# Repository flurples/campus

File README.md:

# campus
mechanical keyboard conversion for a framework 13

build video: https://youtu.be/kGHAUogFsYY

## about
campus is designed to be a drop-in replacement housing for a framework 13 that features a hhkb layout kailh choc mechanical keyboard.

## you will need
- a framework 13 laptop
#### bottom chassis parts
- bottom chassis (cnc)
- bottom-bracket-R, L & M (3d print)
#### input cover parts
- input cover (cnc)
- plate (cnc)
- 3x knobs (cnc)
- 1x touchpad-clamp-R & L (3d print)
- 2x touchpad-clamp-top (3d print)
#### lid parts
- lid (cnc)
- bezel (3d print)
- lid-corner-cap-R & L (3d print)
#### other hardware
- 60x kailh choc switches
- choc stabilizers (2x 2u, 1x 6.25u)
- compatible keycaps (be sure to get 6.25u space, 1.75u shift, etc)
- 3x ec12 low profile encoders
- m1.6 x 3mm heat set inserts
- m2 x 4mm heat set inserts
- m2 x 2.5mm heat set inserts
- 5x m2 x 20mm flat head hex screws (to screw the chassis together)
- 3x m2 x 8mm set screws (for the knobs)
- 4x 1" OD rubber bumpers
- variety of double sided tapes
- epoxy

## build notes
bottom chassis, input cover, lid, knobs, and plate were cnc'd from aluminum. all 3d printed parts were printed in petg to avoid breaking down over the years. heat set inserts for screw holes to mount factory components are installed into the bottom-brackets, which are then epoxied to the bottom-chassis. due to jlcpcb's minimum thickness requirements, the input and lid do not use heat set inserts. instead, the aluminum is directly tapped.

#### the keyboard workaround
the usb hub was too complex and I wasn't able to get it working. because the keyboard was originally meant to connect internally through the usb hub, I ended up simply bypassing the usb hub entirely, bypassing it with a unified daughterboard s1.
in case anyone wants to attempt to diagnose why, I've uploaded the kicad files as is for reference.

## disclaimer
campus is a highly involved project and will require completely tearing down your framework laptop and transplanting all the components into an objectively worse-designed chassis than the factory framework chassis. some features will be lost, for example, the privacy switches built into the webcam module, or the little buttons that lock the expansion cards in place. I am not a professional electronics designer, so expect to perform some janky workarounds to get the laptop functioning as it should. I am not responsible for any issues you may encounter with the build, so please use the files with caution.

I do not sell any products, and I am not affiliated with any vendors who claim to sell my designs. if you choose to support these vendors, I am not responsible for any issues you may encounter with them.

## gallery

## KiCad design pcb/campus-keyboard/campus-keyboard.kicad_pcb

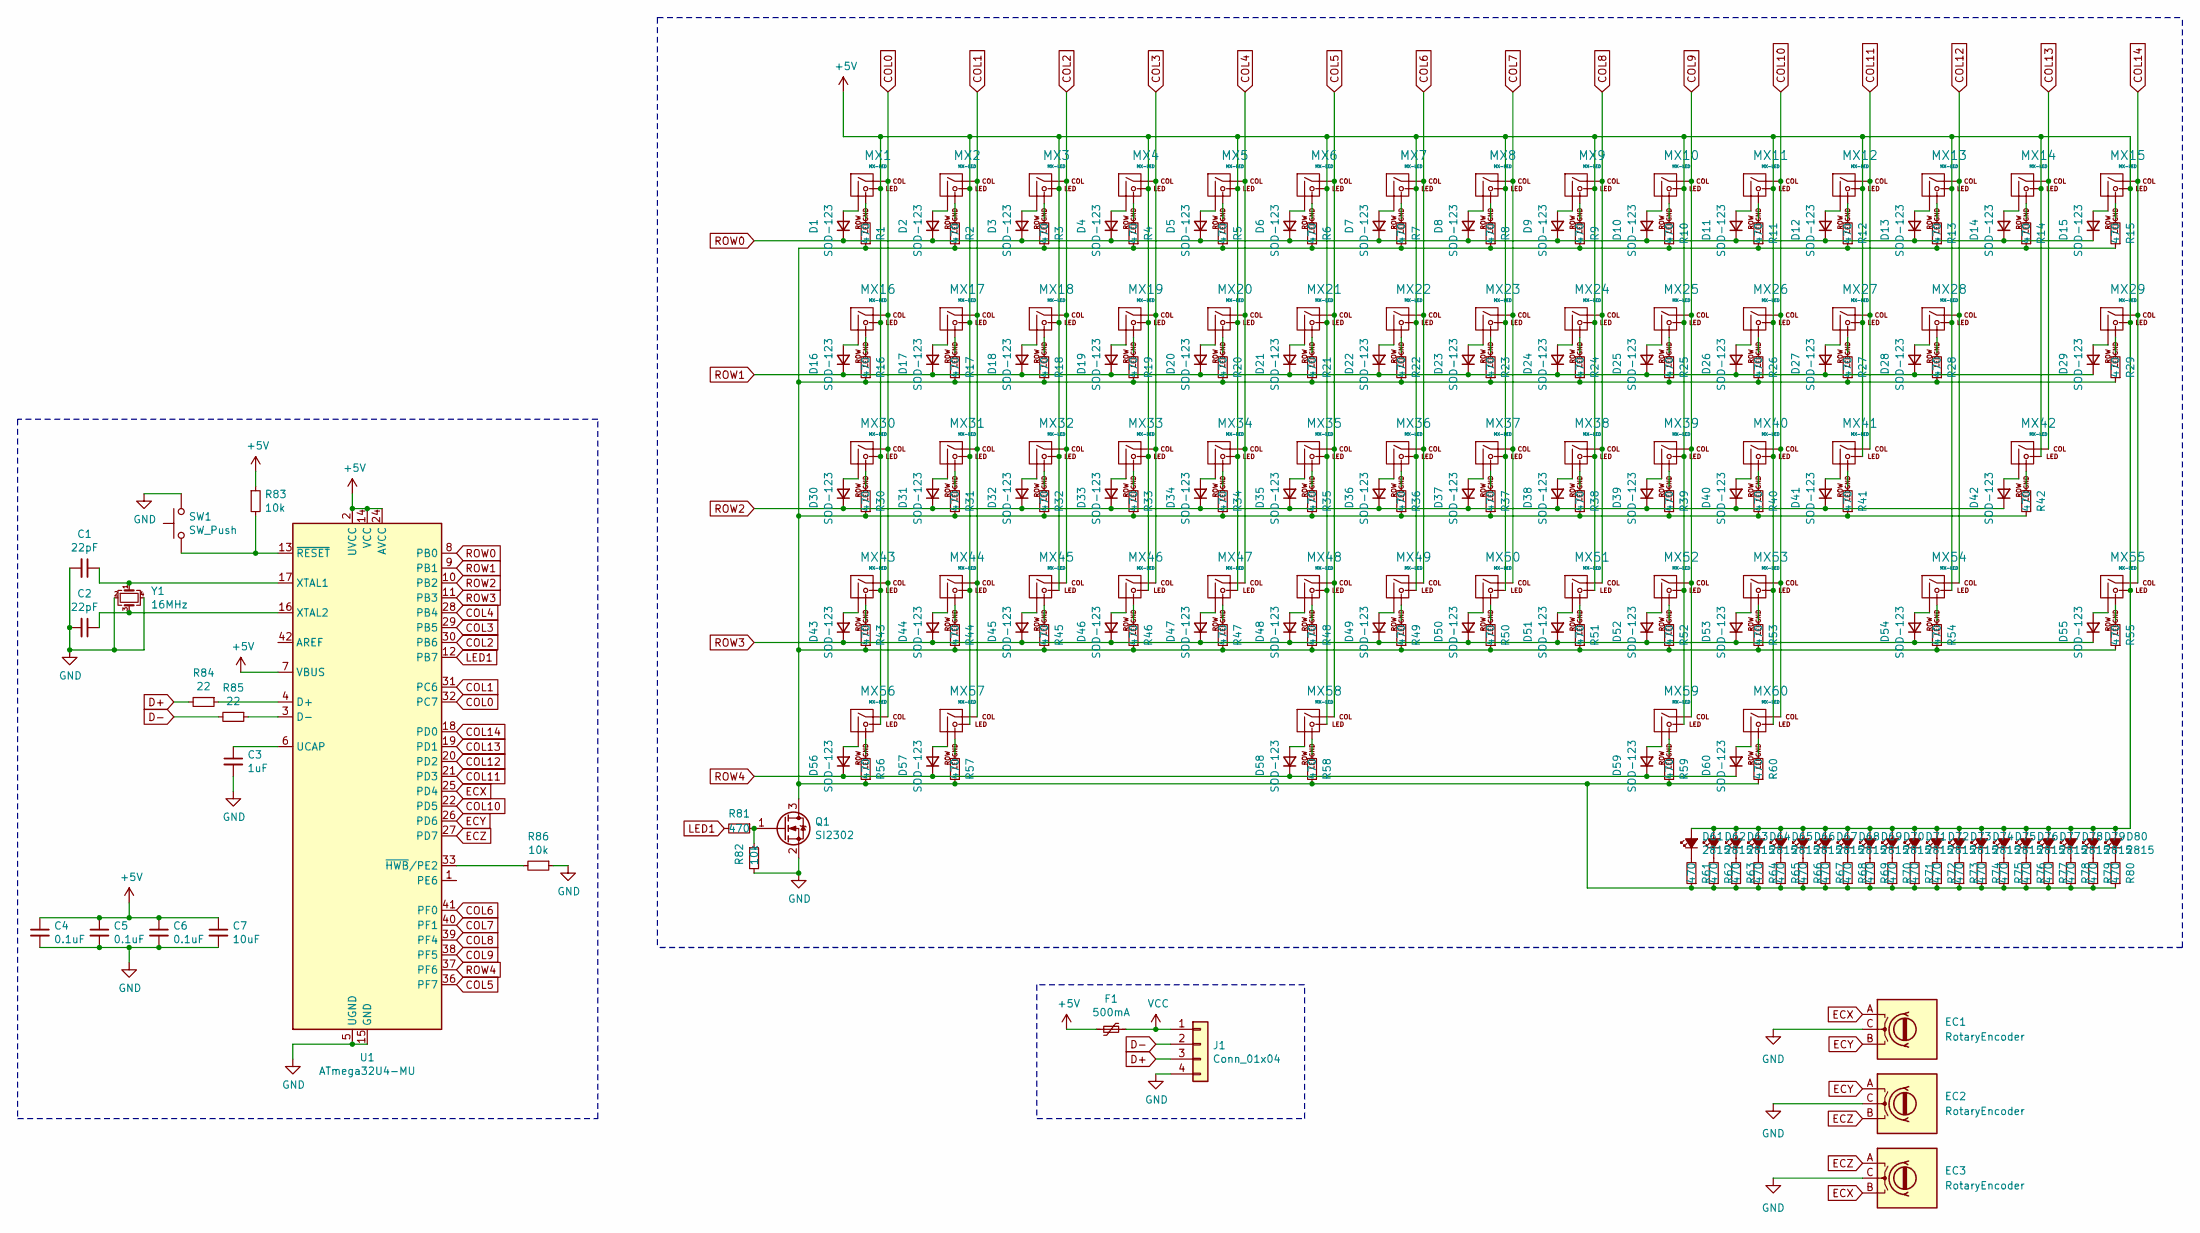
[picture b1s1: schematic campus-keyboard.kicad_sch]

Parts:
C1, C2: 22pF; C_0805_2012Metric
C3: 1uF; C_0805_2012Metric
C4, C5, C6: 0.1uF; C_0805_2012Metric
C7: 10uF; C_0805_2012Metric
D1, D2, D3, D4, D5, D6, D7, D8, D9, D10, D11, D12, D13, D14, D15, D16, D17, D18, D19, D20, D21, D22, D23, D24, D25, D26, D27, D28, D29, D30, D31, D32, D33, D34, D35, D36, D37, D38, D39, D40, D41, D42, D43, D44, D45, D46, D47, D48, D49, D50, D51, D52, D53, D54, D55, D56, D57, D58, D59, D60: SOD-123; D_SOD-123-CenterREF__
D61, D62, D63, D64, D65, D66, D67, D68, D69, D70, D71, D72, D73, D74, D75, D76, D77, D78, D79, D80: 2815; GW JCLPS2.EM
EC1, EC2, EC3: RotaryEncoder; SW3_EC12E1220301_ALPS
F1: 500mA; Fuse_1206_3216Metric
J1: Conn_01x04; Molex_Pico-EZmate_78171-0004_1x04-1MP_P1.20mm_Vertical
MX1, MX2, MX3, MX4, MX5, MX6, MX7, MX8, MX9, MX10, MX11, MX12, MX13, MX14, MX15, MX17, MX18, MX19, MX20, MX21, MX22, MX23, MX24, MX25, MX26, MX27, MX28, MX31, MX32, MX33, MX34, MX35, MX36, MX37, MX38, MX39, MX40, MX41, MX44, MX45, MX46, MX47, MX48, MX49, MX50, MX51, MX52, MX53, MX55: MX-LED; Choc-1u-GW
MX16, MX29: MX-LED; Choc-1.5u-GW
MX30, MX54: MX-LED; Choc-1.75u-GW
MX42, MX43: MX-LED; Choc-2.25u-GW
MX56, MX57, MX59, MX60: MX-LED; Choc-1.25u-GW
MX58: MX-LED; Choc-6.25u-GW
Q1: SI2302; SOT-23
R1, R2, R3, R4, R5, R6, R7, R8, R9, R10, R11, R12, R13, R14, R15, R16, R17, R18, R19, R20, R21, R22, R23, R24, R25, R26, R27, R28, R29, R30, R31, R32, R33, R34, R35, R36, R37, R38, R39, R40, R41, R42, R43, R44, R45, R46, R47, R48, R49, R50, R51, R52, R53, R54, R55, R56, R57, R58, R59, R60, R61, R62, R63, R64, R65, R66, R67, R68, R69, R70, R71, R72, R73, R74, R75, R76, R77, R78, R79, R80, R81: 470; R_0805_2012Metric-CenterREF__
R82, R83, R86: 10k; R_0805_2012Metric-CenterREF__
R84, R85: 22; R_0805_2012Metric-CenterREF__
SW1: SW_Push; SKQG-1155865
U1: ATmega32U4-MU; QFN-44-1EP_7x7mm_P0.5mm_EP5.2x5.2mm
Y1: 16MHz; Crystal_SMD_3225-4Pin_3.2x2.5mm

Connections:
+5V: C4.1, C5.1, C6.1, C7.1, D61.2 (A), D62.2 (A), D63.2 (A), D64.2 (A), D65.2 (A), D66.2 (A), D67.2 (A), D68.2 (A), D69.2 (A), D70.2 (A), D71.2 (A), D72.2 (A), D73.2 (A), D74.2 (A), D75.2 (A), D76.2 (A), D77.2 (A), D78.2 (A), D79.2 (A), D80.2 (A), F1.2, MX1.3 (LED), MX2.3 (LED), MX3.3 (LED), MX4.3 (LED), MX5.3 (LED), MX6.3 (LED), MX7.3 (LED), MX8.3 (LED), MX9.3 (LED), MX10.3 (LED), MX11.3 (LED), MX12.3 (LED), MX13.3 (LED), MX14.3 (LED), MX15.3 (LED), MX16.3 (LED), MX17.3 (LED), MX18.3 (LED), MX19.3 (LED), MX20.3 (LED), MX21.3 (LED), MX22.3 (LED), MX23.3 (LED), MX24.3 (LED), MX25.3 (LED), MX26.3 (LED), MX27.3 (LED), MX28.3 (LED), MX29.3 (LED), MX30.3 (LED), MX31.3 (LED), MX32.3 (LED), MX33.3 (LED), MX34.3 (LED), MX35.3 (LED), MX36.3 (LED), MX37.3 (LED), MX38.3 (LED), MX39.3 (LED), MX40.3 (LED), MX41.3 (LED), MX42.3 (LED), MX43.3 (LED), MX44.3 (LED), MX45.3 (LED), MX46.3 (LED), MX47.3 (LED), MX48.3 (LED), MX49.3 (LED), MX50.3 (LED), MX51.3 (LED), MX52.3 (LED), MX53.3 (LED), MX54.3 (LED), MX55.3 (LED), MX56.3 (LED), MX57.3 (LED), MX58.3 (LED), MX59.3 (LED), MX60.3 (LED), R83.1, U1.2 (UVCC), U1.7 (VBUS), U1.14 (VCC), U1.24 (AVCC), U1.34 (VCC), U1.44 (AVCC)
COL0: MX1.1 (COL), MX16.1 (COL), MX30.1 (COL), MX43.1 (COL), MX56.1 (COL), U1.32 (PC7)
COL1: MX2.1 (COL), MX17.1 (COL), MX31.1 (COL), MX44.1 (COL), MX57.1 (COL), U1.31 (PC6)
COL2: MX3.1 (COL), MX18.1 (COL), MX32.1 (COL), MX45.1 (COL), U1.30 (PB6)
COL3: MX4.1 (COL), MX19.1 (COL), MX33.1 (COL), MX46.1 (COL), U1.29 (PB5)
COL4: MX5.1 (COL), MX20.1 (COL), MX34.1 (COL), MX47.1 (COL), U1.28 (PB4)
COL5: MX6.1 (COL), MX21.1 (COL), MX35.1 (COL), MX48.1 (COL), MX58.1 (COL), U1.36 (PF7)
COL6: MX7.1 (COL), MX22.1 (COL), MX36.1 (COL), MX49.1 (COL), U1.41 (PF0)
COL7: MX8.1 (COL), MX23.1 (COL), MX37.1 (COL), MX50.1 (COL), U1.40 (PF1)
COL8: MX9.1 (COL), MX24.1 (COL), MX38.1 (COL), MX51.1 (COL), U1.39 (PF4)
COL9: MX10.1 (COL), MX25.1 (COL), MX39.1 (COL), MX52.1 (COL), MX59.1 (COL), U1.38 (PF5)
COL10: MX11.1 (COL), MX26.1 (COL), MX40.1 (COL), MX53.1 (COL), MX60.1 (COL), U1.22 (PD5)
COL11: MX12.1 (COL), MX27.1 (COL), MX41.1 (COL), U1.21 (PD3)
COL12: MX13.1 (COL), MX28.1 (COL), MX54.1 (COL), U1.20 (PD2)
COL13: MX14.1 (COL), MX42.1 (COL), U1.19 (PD1)
COL14: MX15.1 (COL), MX29.1 (COL), MX55.1 (COL), U1.18 (PD0)
D+: J1.3, R84.2
D-: J1.2, R85.2
ECX: EC1.1, EC1.A, EC3.3, EC3.B, U1.25 (PD4)
ECY: EC1.3, EC1.B, EC2.1, EC2.A, U1.26 (PD6)
ECZ: EC2.3, EC2.B, EC3.1, EC3.A, U1.27 (PD7)
GND: C1.2, C2.2, C3.2, C4.2, C5.2, C6.2, C7.2, EC1.2, EC1.C, EC2.2, EC2.C, EC3.2, EC3.C, J1.4, Q1.2 (S), R82.2, R86.1, SW1.2, U1.5 (UGND), U1.15 (GND), U1.23 (GND), U1.35 (GND), U1.43 (GND), U1.45 (GND), Y1.2, Y1.4
LED1: R81.2, U1.12 (PB7)
unnamed: D1.2 (A), MX1.2 (ROW)
unnamed: D2.2 (A), MX2.2 (ROW)
unnamed: D3.2 (A), MX3.2 (ROW)
unnamed: D4.2 (A), MX4.2 (ROW)
unnamed: D5.2 (A), MX5.2 (ROW)
unnamed: D6.2 (A), MX6.2 (ROW)
unnamed: D7.2 (A), MX7.2 (ROW)
unnamed: D8.2 (A), MX8.2 (ROW)
unnamed: D9.2 (A), MX9.2 (ROW)
unnamed: D10.2 (A), MX10.2 (ROW)
unnamed: D11.2 (A), MX11.2 (ROW)
unnamed: D12.2 (A), MX12.2 (ROW)
unnamed: D13.2 (A), MX13.2 (ROW)
unnamed: D14.2 (A), MX14.2 (ROW)
unnamed: D15.2 (A), MX15.2 (ROW)
unnamed: D16.2 (A), MX16.2 (ROW)
unnamed: D17.2 (A), MX17.2 (ROW)
unnamed: D18.2 (A), MX18.2 (ROW)
unnamed: D19.2 (A), MX19.2 (ROW)
unnamed: D20.2 (A), MX20.2 (ROW)
unnamed: D21.2 (A), MX21.2 (ROW)
unnamed: D22.2 (A), MX22.2 (ROW)
unnamed: D23.2 (A), MX23.2 (ROW)
unnamed: D24.2 (A), MX24.2 (ROW)
unnamed: D25.2 (A), MX25.2 (ROW)
unnamed: D26.2 (A), MX26.2 (ROW)
unnamed: D27.2 (A), MX27.2 (ROW)
unnamed: D28.2 (A), MX28.2 (ROW)
unnamed: D29.2 (A), MX29.2 (ROW)
unnamed: D30.2 (A), MX30.2 (ROW)
unnamed: D31.2 (A), MX31.2 (ROW)
unnamed: D32.2 (A), MX32.2 (ROW)
unnamed: D33.2 (A), MX33.2 (ROW)
unnamed: D34.2 (A), MX34.2 (ROW)
unnamed: D35.2 (A), MX35.2 (ROW)
unnamed: D36.2 (A), MX36.2 (ROW)
unnamed: D37.2 (A), MX37.2 (ROW)
unnamed: D38.2 (A), MX38.2 (ROW)
unnamed: D39.2 (A), MX39.2 (ROW)
unnamed: D40.2 (A), MX40.2 (ROW)
unnamed: D41.2 (A), MX41.2 (ROW)
unnamed: D42.2 (A), MX42.2 (ROW)
unnamed: D43.2 (A), MX43.2 (ROW)
unnamed: D44.2 (A), MX44.2 (ROW)
unnamed: D45.2 (A), MX45.2 (ROW)
unnamed: D46.2 (A), MX46.2 (ROW)
unnamed: D47.2 (A), MX47.2 (ROW)
unnamed: D48.2 (A), MX48.2 (ROW)
unnamed: D49.2 (A), MX49.2 (ROW)
unnamed: D50.2 (A), MX50.2 (ROW)
unnamed: D51.2 (A), MX51.2 (ROW)
unnamed: D52.2 (A), MX52.2 (ROW)
unnamed: D53.2 (A), MX53.2 (ROW)
unnamed: D54.2 (A), MX54.2 (ROW)
unnamed: D55.2 (A), MX55.2 (ROW)
unnamed: D56.2 (A), MX56.2 (ROW)
unnamed: D57.2 (A), MX57.2 (ROW)
unnamed: D58.2 (A), MX58.2 (ROW)
unnamed: D59.2 (A), MX59.2 (ROW)
unnamed: D60.2 (A), MX60.2 (ROW)
unnamed: D61.1 (K), R61.2
unnamed: D62.1 (K), R62.2
unnamed: D63.1 (K), R63.2
unnamed: D64.1 (K), R64.2
unnamed: D65.1 (K), R65.2
unnamed: D66.1 (K), R66.2
unnamed: D67.1 (K), R67.2
unnamed: D68.1 (K), R68.2
unnamed: D69.1 (K), R69.2
unnamed: D70.1 (K), R70.2
unnamed: D71.1 (K), R71.2
unnamed: D72.1 (K), R72.2
unnamed: D73.1 (K), R73.2
unnamed: D74.1 (K), R74.2
unnamed: D75.1 (K), R75.2
unnamed: D76.1 (K), R76.2
unnamed: D77.1 (K), R77.2
unnamed: D78.1 (K), R78.2
unnamed: D79.1 (K), R79.2
unnamed: D80.1 (K), R80.2
unnamed: MX1.4 (LEDGND), R1.2
unnamed: MX2.4 (LEDGND), R2.2
unnamed: MX3.4 (LEDGND), R3.2
unnamed: MX4.4 (LEDGND), R4.2
unnamed: MX5.4 (LEDGND), R5.2
unnamed: MX6.4 (LEDGND), R6.2
unnamed: MX7.4 (LEDGND), R7.2
unnamed: MX8.4 (LEDGND), R8.2
unnamed: MX9.4 (LEDGND), R9.2
unnamed: MX10.4 (LEDGND), R10.2
unnamed: MX11.4 (LEDGND), R11.2
unnamed: MX12.4 (LEDGND), R12.2
unnamed: MX13.4 (LEDGND), R13.2
unnamed: MX14.4 (LEDGND), R14.2
unnamed: MX15.4 (LEDGND), R15.2
unnamed: MX16.4 (LEDGND), R16.2
unnamed: MX17.4 (LEDGND), R17.2
unnamed: MX18.4 (LEDGND), R18.2
unnamed: MX19.4 (LEDGND), R19.2
unnamed: MX20.4 (LEDGND), R20.2
unnamed: MX21.4 (LEDGND), R21.2
unnamed: MX22.4 (LEDGND), R22.2
unnamed: MX23.4 (LEDGND), R23.2
unnamed: MX24.4 (LEDGND), R24.2
unnamed: MX25.4 (LEDGND), R25.2
unnamed: MX26.4 (LEDGND), R26.2
unnamed: MX27.4 (LEDGND), R27.2
unnamed: MX28.4 (LEDGND), R28.2
unnamed: MX29.4 (LEDGND), R29.2
unnamed: MX30.4 (LEDGND), R30.2
unnamed: MX31.4 (LEDGND), R31.2
unnamed: MX32.4 (LEDGND), R32.2
unnamed: MX33.4 (LEDGND), R33.2
unnamed: MX34.4 (LEDGND), R34.2
unnamed: MX35.4 (LEDGND), R35.2
unnamed: MX36.4 (LEDGND), R36.2
unnamed: MX37.4 (LEDGND), R37.2
unnamed: MX38.4 (LEDGND), R38.2
unnamed: MX39.4 (LEDGND), R39.2
unnamed: MX40.4 (LEDGND), R40.2
unnamed: MX41.4 (LEDGND), R41.2
unnamed: MX42.4 (LEDGND), R42.2
unnamed: MX43.4 (LEDGND), R43.2
unnamed: MX44.4 (LEDGND), R44.2
unnamed: MX45.4 (LEDGND), R45.2
unnamed: MX46.4 (LEDGND), R46.2
unnamed: MX47.4 (LEDGND), R47.2
unnamed: MX48.4 (LEDGND), R48.2
unnamed: MX49.4 (LEDGND), R49.2
unnamed: MX50.4 (LEDGND), R50.2
unnamed: MX51.4 (LEDGND), R51.2
unnamed: MX52.4 (LEDGND), R52.2
unnamed: MX53.4 (LEDGND), R53.2
unnamed: MX54.4 (LEDGND), R54.2
unnamed: MX55.4 (LEDGND), R55.2
unnamed: MX56.4 (LEDGND), R56.2
unnamed: MX57.4 (LEDGND), R57.2
unnamed: MX58.4 (LEDGND), R58.2
unnamed: MX59.4 (LEDGND), R59.2
unnamed: MX60.4 (LEDGND), R60.2
unnamed: Q1.3 (D), R1.1, R2.1, R3.1, R4.1, R5.1, R6.1, R7.1, R8.1, R9.1, R10.1, R11.1, R12.1, R13.1, R14.1, R15.1, R16.1, R17.1, R18.1, R19.1, R20.1, R21.1, R22.1, R23.1, R24.1, R25.1, R26.1, R27.1, R28.1, R29.1, R30.1, R31.1, R32.1, R33.1, R34.1, R35.1, R36.1, R37.1, R38.1, R39.1, R40.1, R41.1, R42.1, R43.1, R44.1, R45.1, R46.1, R47.1, R48.1, R49.1, R50.1, R51.1, R52.1, R53.1, R54.1, R55.1, R56.1, R57.1, R58.1, R59.1, R60.1, R61.1, R62.1, R63.1, R64.1, R65.1, R66.1, R67.1, R68.1, R69.1, R70.1, R71.1, R72.1, R73.1, R74.1, R75.1, R76.1, R77.1, R78.1, R79.1, R80.1
unnamed: Q1.1 (G), R81.1, R82.1
unnamed: R84.1, U1.4 (D+)
unnamed: R85.1, U1.3 (D-)
unnamed: C3.1, U1.6 (UCAP)
unnamed: C1.1, U1.17 (XTAL1), Y1.1
unnamed: C2.1, U1.16 (XTAL2), Y1.3
unnamed: R86.2, U1.33 (~HWB/PE2)
unnamed: R83.2, SW1.1, U1.13 (~RESET)
ROW0: D1.1 (K), D2.1 (K), D3.1 (K), D4.1 (K), D5.1 (K), D6.1 (K), D7.1 (K), D8.1 (K), D9.1 (K), D10.1 (K), D11.1 (K), D12.1 (K), D13.1 (K), D14.1 (K), D15.1 (K), U1.8 (PB0)
ROW1: D16.1 (K), D17.1 (K), D18.1 (K), D19.1 (K), D20.1 (K), D21.1 (K), D22.1 (K), D23.1 (K), D24.1 (K), D25.1 (K), D26.1 (K), D27.1 (K), D28.1 (K), D29.1 (K), U1.9 (PB1)
ROW2: D30.1 (K), D31.1 (K), D32.1 (K), D33.1 (K), D34.1 (K), D35.1 (K), D36.1 (K), D37.1 (K), D38.1 (K), D39.1 (K), D40.1 (K), D41.1 (K), D42.1 (K), U1.10 (PB2)
ROW3: D43.1 (K), D44.1 (K), D45.1 (K), D46.1 (K), D47.1 (K), D48.1 (K), D49.1 (K), D50.1 (K), D51.1 (K), D52.1 (K), D53.1 (K), D54.1 (K), D55.1 (K), U1.11 (PB3)
ROW4: D56.1 (K), D57.1 (K), D58.1 (K), D59.1 (K), D60.1 (K), U1.37 (PF6)
VCC: F1.1, J1.1

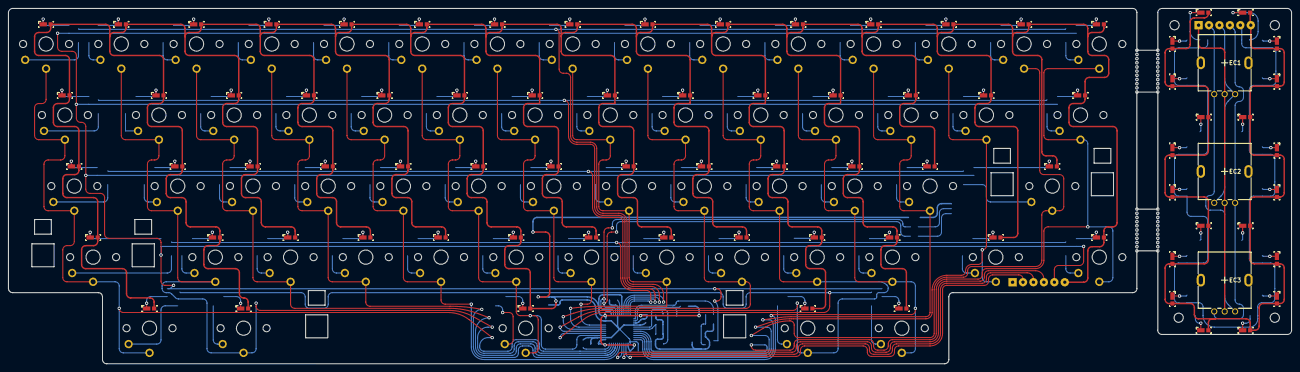
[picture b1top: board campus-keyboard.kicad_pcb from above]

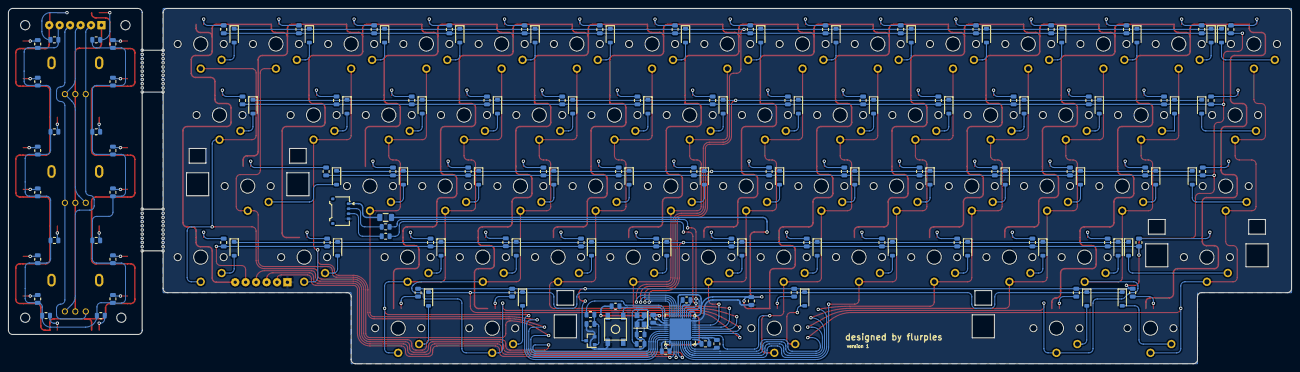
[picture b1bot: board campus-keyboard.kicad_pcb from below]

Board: 2 copper layers, 307.0 x 85.0 mm, 242 parts (159 on the bottom side), 178 nets.

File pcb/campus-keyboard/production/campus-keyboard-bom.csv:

Comment,Designator,Footprint,LCSC Part Number
22pF,"C1,C2",Capacitor_SMD:C_0805_2012Metric,C1804
1uF,C3,Capacitor_SMD:C_0805_2012Metric,C28323
0.1uF,"C4,C5,C6",Capacitor_SMD:C_0805_2012Metric,C1711
10uF,C7,Capacitor_SMD:C_0805_2012Metric,C1713
SOD-123,"D1,D2,D3,D4,D5,D6,D7,D8,D9,D10,D11,D12,D13,D14,D15,D16,D17,D18,D19,D20,D21,D22,D23,D24,D25,D26,D27,D28,D29,D30,D31,D32,D33,D34,D35,D36,D37,D38,D39,D40,D41,D42,D43,D44,D45,D46,D47,D48,D49,D50,D51,D52,D53,D54,D55,D56,D57,D58,D59,D60",Diode_SMD:D_SOD-123,C2099
500mA,F1,Fuse:Fuse_1206_3216Metric,C720075
Conn_01x04,J1,Connector_Molex:Molex_Pico-EZmate_78171-0004_1x04-1MP_P1.20mm_Vertical,C588524
SI2302,Q1,Package_TO_SOT_SMD:SOT-23,C2891732
470,"R1,R2,R3,R4,R5,R6,R7,R8,R9,R10,R11,R12,R13,R14,R15,R16,R17,R18,R19,R20,R21,R22,R23,R24,R25,R26,R27,R28,R29,R30,R31,R32,R33,R34,R35,R36,R37,R38,R39,R40,R41,R42,R43,R44,R45,R46,R47,R48,R49,R50,R51,R52,R53,R54,R55,R56,R57,R58,R59,R60,R61,R62,R63,R64,R65,R66,R67,R68,R69,R70,R71,R72,R73,R74,R75,R76,R77,R78,R79,R80,R81",campus-parts:R_0805_2012Metric,C17710
10k,"R82,R83,R86",campus-parts:R_0805_2012Metric,C17414
22,"R84,R85",campus-parts:R_0805_2012Metric,C17561
SW_Push,SW1,random-keyboard-parts:SKQG-1155865,C5140332
ATmega32U4-MU,U1,Package_DFN_QFN:QFN-44-1EP_7x7mm_P0.5mm_EP5.2x5.2mm,C112161
16MHz,Y1,Crystal:Crystal_SMD_3225-4Pin_3.2x2.5mm,C13738

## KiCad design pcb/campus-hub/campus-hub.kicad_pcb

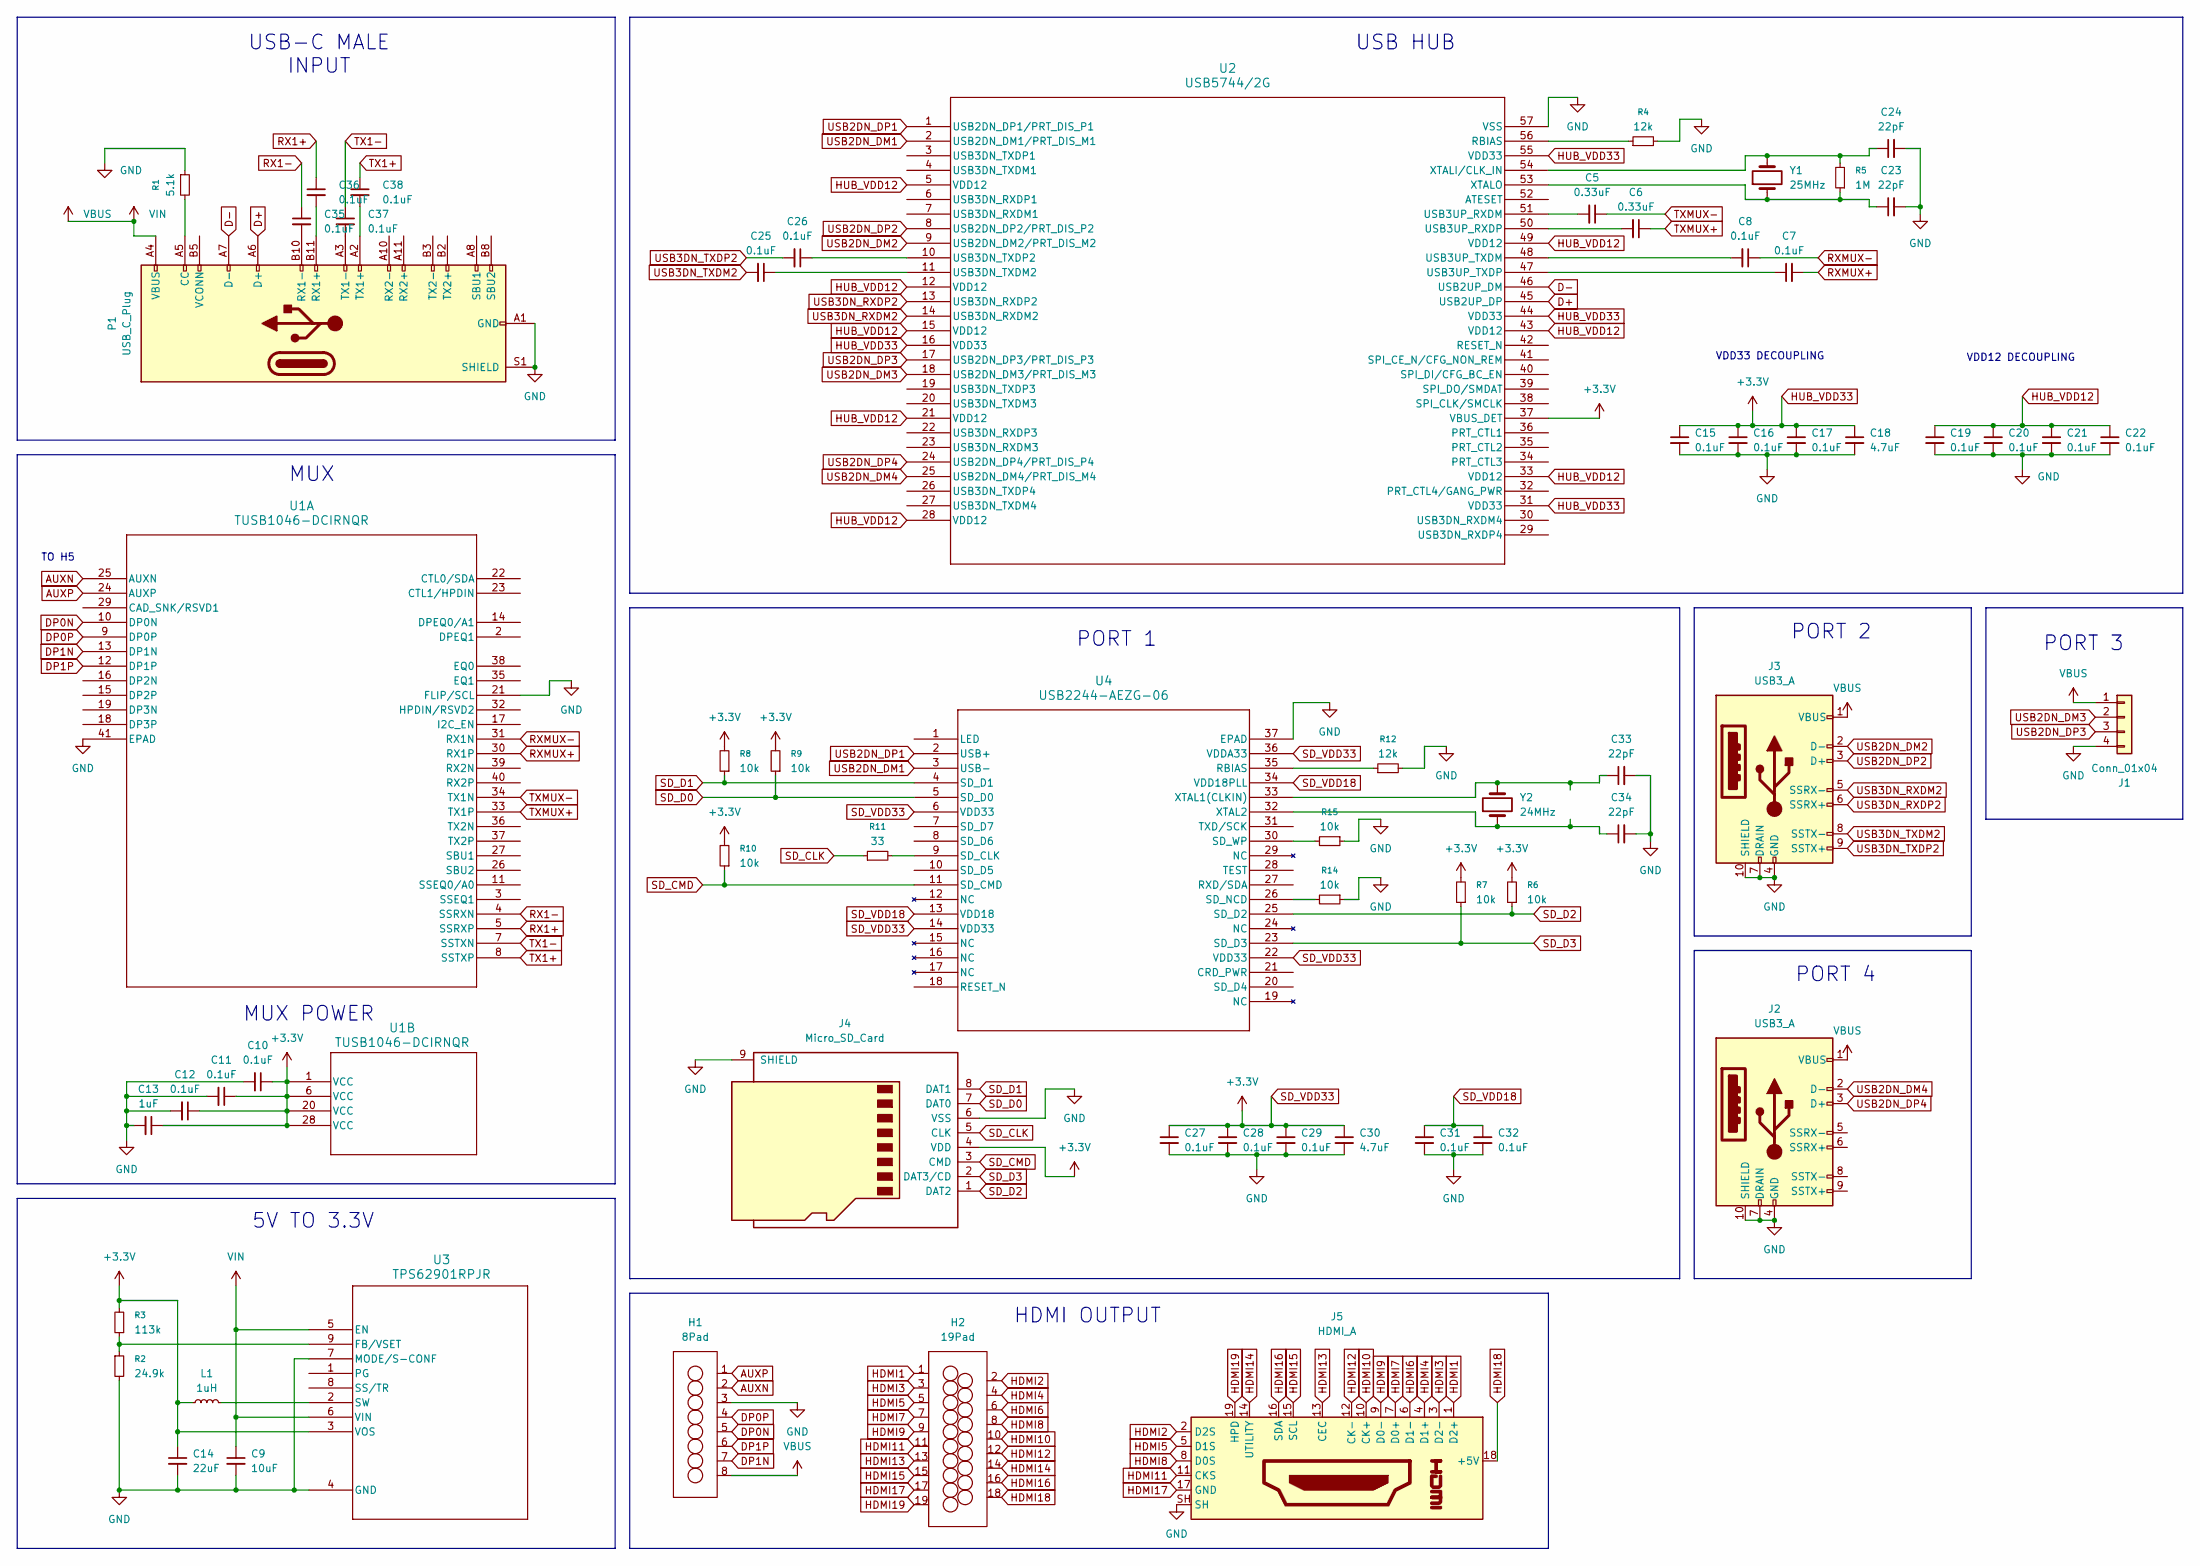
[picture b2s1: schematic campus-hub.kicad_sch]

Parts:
C5, C6: 0.33uF; C_0805_2012Metric
C7, C8, C10, C11, C12, C15, C16, C17, C19, C20, C21, C22, C25, C26, C27, C28, C29, C31, C32, C35, C36, C37, C38: 0.1uF; C_0805_2012Metric
C9: 10uF; C_0805_2012Metric
C13: 1uF; C_0805_2012Metric
C14: 22uF; C_0805_2012Metric
C18, C30: 4.7uF; C_0805_2012Metric
C23, C24, C33, C34: 22pF; C_0805_2012Metric
H1: 8Pad
H2: 19Pad
J1: Conn_01x04; Molex_Pico-EZmate_78171-0004_1x04-1MP_P1.20mm_Vertical
J2, J3: USB3_A; 692121230100
J4: Micro_SD_Card; 104031-0811_MOL
J5: HDMI_A; SAMESKY_HD07-19-RVS-MSMT-TR
L1: 1uH; L_1008_2520Metric
P1: USB_C_Plug; MOLEX_1054440001
R1: 5.1k; R_0805_2012Metric
R2: 24.9k; R_0805_2012Metric
R3: 113k; R_0805_2012Metric
R4, R12: 12k; R_0805_2012Metric
R5: 1M; R_0805_2012Metric
R6, R7, R8, R9, R10, R14, R15: 10k; R_0805_2012Metric
R11: 33; R_0805_2012Metric
U1: TUSB1046-DCIRNQR; RNQ40_TEX
U2: USB5744/2G; VQFN56_2G_MCH
U3: TPS62901RPJR; QFN_902RPJR_TEX
U4: USB2244-AEZG-06; QFN36_6X6MC_MCH
Y1: 25MHz; Crystal_SMD_3225-4Pin_3.2x2.5mm
Y2: 24MHz; Crystal_SMD_3225-4Pin_3.2x2.5mm

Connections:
AUXN: H1.2, U1.25 (AUXN)
AUXP: H1.1, U1.24 (AUXP)
D+: P1.A6 (D+), U2.45 (USB2UP_DP)
D-: P1.A7 (D-), U2.46 (USB2UP_DM)
DP0N: H1.5, U1.10 (DP0N)
DP0P: H1.4, U1.9 (DP0P)
DP1N: H1.7, U1.13 (DP1N)
DP1P: H1.6, U1.12 (DP1P)
GND: C9.2, C10.2, C11.2, C12.2, C13.2, C14.2, C15.2, C16.2, C17.2, C18.2, C19.2, C20.2, C21.2, C22.2, C23.2, C24.2, C27.2, C28.2, C29.2, C30.2, C31.2, C32.2, C33.2, C34.2, H1.3, J1.4, J2.4 (GND), J2.7 (DRAIN), J2.10 (SHIELD), J3.4 (GND), J3.7 (DRAIN), J3.10 (SHIELD), J4.6 (VSS), J4.9 (SHIELD), J4.11, J4.12, J4.13, J4.14, J5.SH, P1.A1 (GND), P1.A12 (GND), P1.B1 (GND), P1.B12 (GND), P1.S1 (SHIELD), P1.SH1, R1.1, R2.2, R4.2, R12.2, R14.1, R15.1, U1.21 (FLIP/SCL), U1.41 (EPAD), U2.57 (VSS), U3.4 (GND), U3.7 (MODE/S-CONF), U4.37 (EPAD), Y1.2, Y1.4, Y2.2, Y2.4
HDMI1: H2.1, J5.1 (D2+)
HDMI2: H2.2, J5.2 (D2S)
HDMI3: H2.3, J5.3 (D2-)
HDMI4: H2.4, J5.4 (D1+)
HDMI5: H2.5, J5.5 (D1S)
HDMI6: H2.6, J5.6 (D1-)
HDMI7: H2.7, J5.7 (D0+)
HDMI8: H2.8, J5.8 (D0S)
HDMI9: H2.9, J5.9 (D0-)
HDMI10: H2.10, J5.10 (CK+)
HDMI11: H2.11, J5.11 (CKS)
HDMI12: H2.12, J5.12 (CK-)
HDMI13: H2.13, J5.13 (CEC)
HDMI14: H2.14, J5.14 (UTILITY)
HDMI15: H2.15, J5.15 (SCL)
HDMI16: H2.16, J5.16 (SDA)
HDMI17: H2.17, J5.17 (GND)
HDMI18: H2.18, J5.18 (+5V)
HDMI19: H2.19, J5.19 (HPD)
HUB_VDD12: C19.1, C20.1, C21.1, C22.1, U2.5 (VDD12), U2.12 (VDD12), U2.15 (VDD12), U2.21 (VDD12), U2.28 (VDD12), U2.33 (VDD12), U2.43 (VDD12), U2.49 (VDD12)
HUB_VDD33: C10.1, C11.1, C12.1, C13.1, C14.1, C15.1, C16.1, C17.1, C18.1, C27.1, C28.1, C29.1, C30.1, J4.4 (VDD), L1.1, R3.2, R6.2, R7.2, R8.2, R9.2, R10.2, U1.1 (VCC), U1.6 (VCC), U1.20 (VCC), U1.28 (VCC), U2.16 (VDD33), U2.31 (VDD33), U2.37 (VBUS_DET), U2.44 (VDD33), U2.55 (VDD33), U3.3 (VOS), U4.6 (VDD33), U4.14 (VDD33), U4.22 (VDD33), U4.36 (VDDA33)
unnamed: P1.A5 (CC), R1.2
unnamed: C36.2, P1.B11 (RX1+)
unnamed: C35.2, P1.B10 (RX1-)
unnamed: C38.2, P1.A2 (TX1+)
unnamed: C37.2, P1.A3 (TX1-)
unnamed: R4.1, U2.56 (RBIAS)
unnamed: C25.1, U2.11 (USB3DN_TXDM2)
unnamed: C26.1, U2.10 (USB3DN_TXDP2)
unnamed: C5.2, U2.51 (USB3UP_RXDM)
unnamed: C6.2, U2.50 (USB3UP_RXDP)
unnamed: C8.2, U2.48 (USB3UP_TXDM)
unnamed: C7.1, U2.47 (USB3UP_TXDP)
unnamed: C24.1, R5.2, U2.54 (XTALI/CLK_IN), Y1.3
unnamed: C23.1, R5.1, U2.53 (XTALO), Y1.1
unnamed: R2.1, R3.1, U3.9 (FB/VSET)
unnamed: L1.2, U3.2 (SW)
unnamed: R12.1, U4.35 (RBIAS)
unnamed: R11.2, U4.9 (SD_CLK)
unnamed: R14.2, U4.26 (SD_NCD)
unnamed: R15.2, U4.30 (SD_WP)
unnamed: C33.1, U4.33 (XTAL1(CLKIN)), Y2.3
unnamed: C34.1, U4.32 (XTAL2), Y2.1
RX1+: C36.1, U1.5 (SSRXP)
RX1-: C35.1, U1.4 (SSRXN)
RXMUX+: C7.2, U1.30 (RX1P)
RXMUX-: C8.1, U1.31 (RX1N)
SD_CLK: J4.5 (CLK), R11.1
SD_CMD: J4.3 (CMD), R10.1, U4.11 (SD_CMD)
SD_D0: J4.7 (DAT0), R9.1, U4.5 (SD_D0)
SD_D1: J4.8 (DAT1), R8.1, U4.4 (SD_D1)
SD_D2: J4.1 (DAT2), R6.1, U4.25 (SD_D2)
SD_D3: J4.2 (DAT3/CD), R7.1, U4.23 (SD_D3)
SD_VDD18: C31.1, C32.1, U4.13 (VDD18), U4.34 (VDD18PLL)
TX1+: C38.1, U1.8 (SSTXP)
TX1-: C37.1, U1.7 (SSTXN)
TXMUX+: C6.1, U1.33 (TX1P)
TXMUX-: C5.1, U1.34 (TX1N)
USB2DN_DM1: U2.2 (USB2DN_DM1/PRT_DIS_M1), U4.3 (USB-)
USB2DN_DM2: J3.2 (D-), U2.9 (USB2DN_DM2/PRT_DIS_M2)
USB2DN_DM3: J1.2, U2.18 (USB2DN_DM3/PRT_DIS_M3)
USB2DN_DM4: J2.2 (D-), U2.25 (USB2DN_DM4/PRT_DIS_M4)
USB2DN_DP1: U2.1 (USB2DN_DP1/PRT_DIS_P1), U4.2 (USB+)
USB2DN_DP2: J3.3 (D+), U2.8 (USB2DN_DP2/PRT_DIS_P2)
USB2DN_DP3: J1.3, U2.17 (USB2DN_DP3/PRT_DIS_P3)
USB2DN_DP4: J2.3 (D+), U2.24 (USB2DN_DP4/PRT_DIS_P4)
USB3DN_RXDM2: J3.5 (SSRX-), U2.14 (USB3DN_RXDM2)
USB3DN_RXDP2: J3.6 (SSRX+), U2.13 (USB3DN_RXDP2)
USB3DN_TXDM2: C25.2, J3.8 (SSTX-)
USB3DN_TXDP2: C26.2, J3.9 (SSTX+)
VBUS: C9.1, H1.8, J1.1, J2.1 (VBUS), J3.1 (VBUS), P1.A4 (VBUS), P1.A9 (VBUS), P1.B4 (VBUS), P1.B9 (VBUS), U3.5 (EN), U3.6 (VIN)

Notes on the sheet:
PORT 2
VDD12 DECOUPLING
USB HUB
HDMI OUTPUT
PORT 4
MUX
MUX POWER
USB-C MALE INPUT
5V TO 3.3V
TO H5
PORT 1
PORT 3
VDD33 DECOUPLING

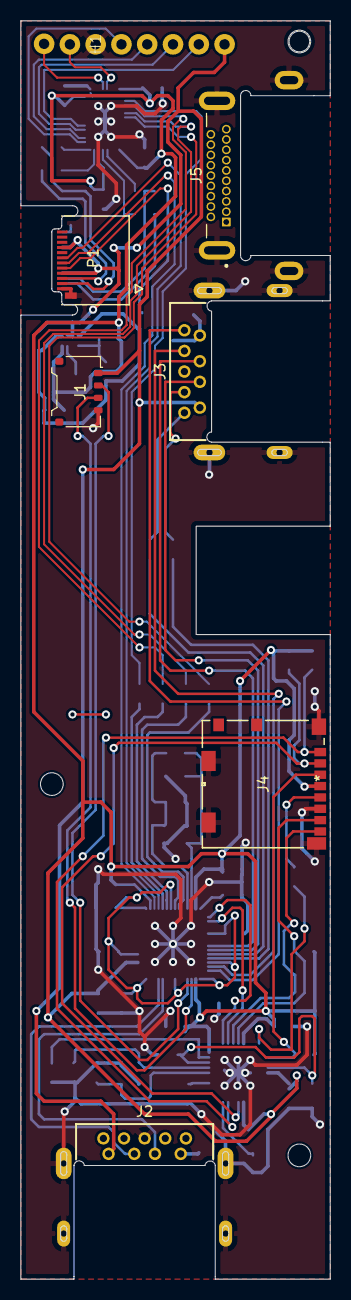
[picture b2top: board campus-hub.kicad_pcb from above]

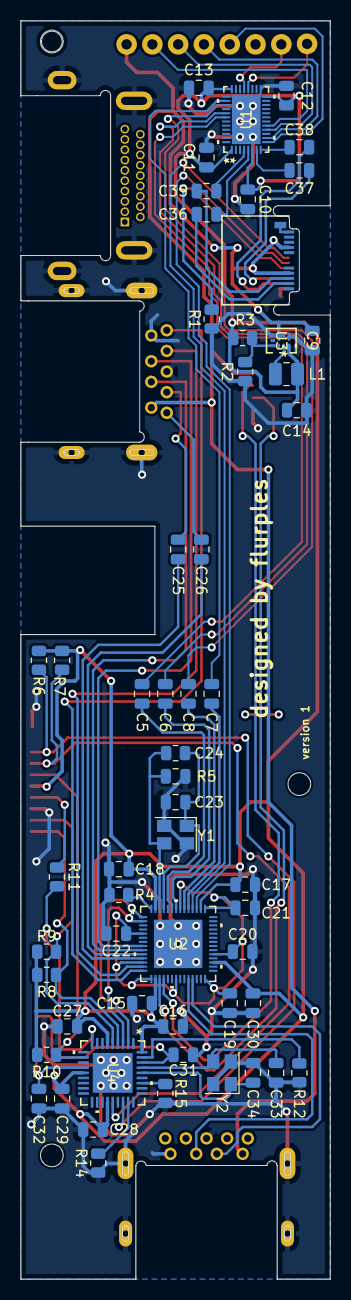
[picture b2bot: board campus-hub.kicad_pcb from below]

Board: 2 copper layers, 30.0 x 122.0 mm, 62 parts (55 on the bottom side), 61 nets.

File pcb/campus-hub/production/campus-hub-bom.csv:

Comment,Designator,Footprint,LCSC Part Number
10uF,C9,Capacitor_SMD:C_0805_2012Metric,C1713
1uF,C13,Capacitor_SMD:C_0805_2012Metric,C28323
22uF,C14,Capacitor_SMD:C_0805_2012Metric,C5674
4.7uF,"C18,C30",Capacitor_SMD:C_0805_2012Metric,C1779
22pF,"C23,C24,C33,C34",Capacitor_SMD:C_0805_2012Metric,C1804
0.33uF,"C5,C6",Capacitor_SMD:C_0805_2012Metric,C73142
0.1uF,"C7,C8,C10,C11,C12,C15,C16,C17,C19,C20,C21,C22,C25,C26,C27,C28,C29,C31,C32,C35,C36,C37,C38",Capacitor_SMD:C_0805_2012Metric,C1711
1uH,L1,Inductor_SMD:L_1008_2520Metric,C5179444
5.1k,R1,Resistor_SMD:R_0805_2012Metric,C27834
24.9k,R2,Resistor_SMD:R_0805_2012Metric,C17571
113k,R3,Resistor_SMD:R_0805_2012Metric,C17424
1M,R5,Resistor_SMD:R_0805_2012Metric,C2889485
33,R11,Resistor_SMD:R_0805_2012Metric,C17634
12k,"R4,R12",Resistor_SMD:R_0805_2012Metric,C17444
10k,"R6,R7,R8,R9,R10,R14,R15",Resistor_SMD:R_0805_2012Metric,C17414
TUSB1046-DCIRNQR,U1,campus-parts:RNQ40_TEX,C2151061
USB5744/2G,U2,campus-parts:VQFN56_2G_MCH,C633621
TPS62901RPJR,U3,campus-parts:QFN_902RPJR_TEX,C2864847
USB2244-AEZG-06,U4,campus-parts:QFN36_6X6MC_MCH,C2674043
25MHz,Y1,Crystal:Crystal_SMD_3225-4Pin_3.2x2.5mm,C9006
24MHz,Y2,Crystal:Crystal_SMD_3225-4Pin_3.2x2.5mm,C7294566
